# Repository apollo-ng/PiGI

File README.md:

# PiGI - A Raspberry Pi Geiger-Mueller Interface

The PiGI is built as a ready-to-go drop-in module for the Raspberry Pi to transform it
into a versatile geiger counter to measure/monitor radioactivity. It will generate the
required high voltage the counting tubes need to operate and it will safely invert the
counting impulses to a falling edge, detectable by a GPIO Pin on the PI. But it's also
designed in such a universal way in order to be  very hackable. Basically it can be
connected to any processing system that can detect falling edges like:

  * Arduino
  * ATMega
  * PIC
  * Other embedded Linux ARM/MIPS systems with GPIO Inputs (GNUBLIN, Netus G20 etc.)

## Specifications

  * 40x43mm board
  * Very low energy consumption (<2mA @ 0.09uSv/h local dose rate)
  * Cathode counting
  * Low BOM count / small footprint
  * Very cheap design: Prototype costs per board -> EUR15 / High Volume Production < 10 EUR
  * Dual stackable for low/high dosis counting with 2 tubes
  * Open-Source Hardware/Software

## Hardware

  * Schematics
  * Board designs
  * Released under CERN OHL 1.2

## Software

### Features ###

  * Live Status
  * Live (15min/60min/24h) Graphs
  * Analog gauge
  * Ion Trace Visualizer
  * History
  * Tick Simulator (For show and development)
  * Hardware RNG entropy generator
  * More to come
  * Released under GPL V3

### Screenshots ###

#### Main instrument panel

#### History instrument panel

#### Ion trace visualizer

## Website & Contact

[https://apollo.open-resource.org/lab:pigi](https://apollo.open-resource.org/lab:pigi)

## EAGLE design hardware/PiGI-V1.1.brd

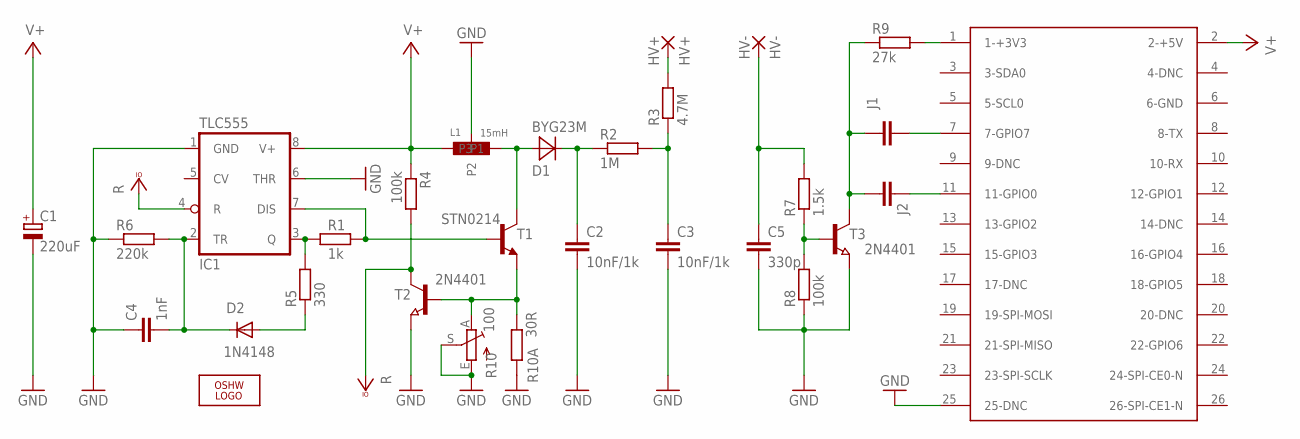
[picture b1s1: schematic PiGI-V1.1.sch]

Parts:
C1: 220uF; 153CLV-0810
C2, C3: 10nF/1k; C1206
C4: 1nF; C0805
C5: 330p; C0805
D1: BYG23M; SMA
D2: 1N4148; SOD-123_MINI-SMA
HV+: HV+; SMD2,54-5,08
HV-: HV-; SMD2,54-5,08
IC1: TLC555; SO08
J1, J2: C-EUC0805; C0805
L1: 15mH; 1200LRS
LOGO1: OSHW_LOGO_FILLX0150-NT; OSHW_FILLX150_NOTEXT
PI-GIV1.0: RASPBERRY-PI
R1: 1k; M0805
R2: 1M; R1206
R3: 4.7M; R1206
R4, R8: 100k; R0805
R5: 330; R0805
R6: 220k; R0805
R7: 1.5k; R0805
R9: 27k; R0805
R10: 100; RJ9W
R10A: 30R; M0805
T1: STN0214; SOT223
T2, T3: 2N4401; SOT23

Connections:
DIS: IC1.7 (DIS), R1.2, T1.1 (B)
GND: C1.-, C2.2, C3.2, C4.1, C5.2, IC1.1 (GND), IC1.6 (THR), L1.P4 (P2), PI-GIV1.0.25 (25-DNC), R6.1, R8.1, R10.E (A), R10.S, R10A.1, T2.2 (E), T3.2 (E)
unnamed: IC1.3 (Q), R1.1, R5.2
unnamed: D2.A, R5.1
unnamed: C2.1, D1.C, R2.1
unnamed: PI-GIV1.0.1 (1-+3V3), R9.2
unnamed: C4.2, D2.C, IC1.2 (TR), R6.2
unnamed: D1.A, L1.P3, T1.4 (C)
unnamed: R10.A (E), R10A.2, T1.3 (E), T2.1 (B)
unnamed: C3.1, R2.2, R3.1
unnamed: R7.1, R8.2, T3.1 (B)
unnamed: J1.2, J2.2, R9.1, T3.3 (C)
unnamed: C5.1, HV-.1, R7.2
unnamed: HV+.1, R3.2
unnamed: J1.1, PI-GIV1.0.7 (7-GPIO7)
unnamed: J2.1, PI-GIV1.0.11 (11-GPIO0)
V+: C1.+, IC1.8 (V+), L1.P1, PI-GIV1.0.2 (2-+5V), R4.1
VCCIO: IC1.4 (R), R4.2, T2.3 (C)

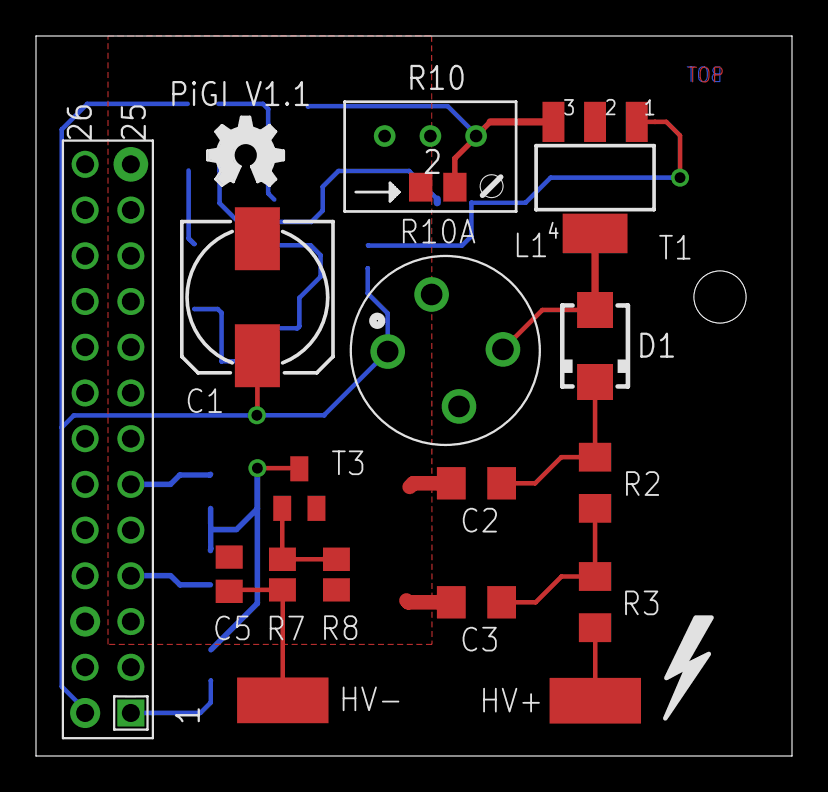
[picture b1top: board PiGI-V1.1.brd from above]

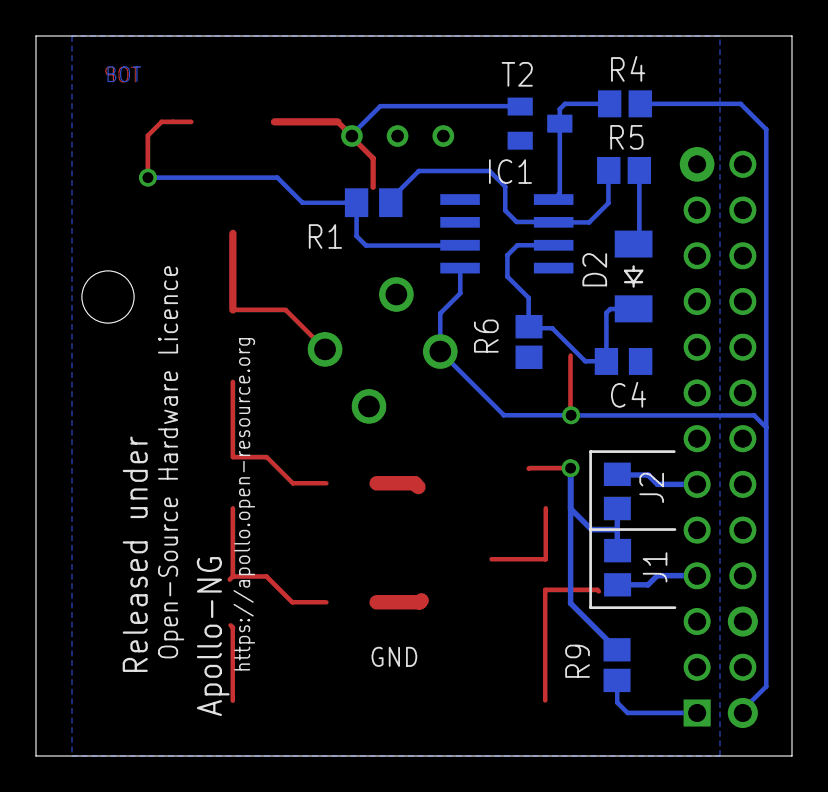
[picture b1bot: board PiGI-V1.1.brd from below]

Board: 2 copper layers, 42.0 x 40.0 mm, 29 parts (11 on the bottom side), 18 nets.

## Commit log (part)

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2013-06-08 Added V1.0 Board for the prototypes
2013-06-08 Added V1.1 (pre-production state)
2013-06-08 Added simple couter example
2013-06-08 Added some basic initial docs
2013-06-08 Updated docs
2013-06-08 More doc updates
2013-06-09 Minor position modifications of t/bnames placement on the board and clean up of schematics
2013-06-23 Added HD images of prototype board V1.0
2013-06-30 Added Image to README.md
2013-07-03 Added daemon skelleton harness (counterd4)
2013-07-03 Added software arch overview
2013-07-23 typo fixes
2014-02-09 added picoreflow stuff as boilerplate
2014-02-09 added gitignore
2014-02-09 public/index.html
2014-02-09 Fixed absoloute path asset bug
2014-02-09 Updated index.html and css for pigi basics
2014-02-09 audio example
2014-02-09 sound working, yay
2014-02-09 webserver working again on non-pi devices
2014-02-09 minimal counter simulation
2014-02-09 cpm logic
2014-02-09 included pigi gpio
2014-02-09 More pigi UI changes
2014-02-09 cpm values over websocket
2014-02-09 Added CPM update to websocket
2014-02-09 different cpm/cps calculation
2014-02-09 Testing CPS
2014-02-09 dont send only zeros for cps %)
2014-02-10 Updated README in example archive to point to pigid
2014-02-10 added counterd.py to examples
2014-02-10 adapted config to geigercounter
2014-02-10 Added Audio en/disable and counter toggling (CPM/CPS)
2014-02-10 multiclient, more values
2014-02-10 config parameter bugfix
2014-02-10 Adapted INES level indicator for quick situation determination
2014-02-10 Alternative construct for the head display (not active yet)
2014-02-10 refactoring
2014-02-10 refactoring to two sockets, audio toggle working again
2014-02-10 Added README
2014-02-10 basic logging and log delivery
2014-02-10 wrapping of loglines in history obj
2014-02-10 add timestamp to log update
2014-02-10 Added flot.time.js
2014-02-10 delay first log line after start
2014-02-10 Trying to integrate INES ruleset
2014-02-10 only send log of last 15 min
2014-02-10 only show rolling last 15 min in graph
2014-02-10 Added favicon.ico
2014-02-10 serve favicon
2014-02-11 cleanup and refeactoring
2014-02-11 init script added
2014-02-11 absolute path fixes, initscript works :)
2014-02-11 Updated README with current deps & install/usage instructions
2014-02-14 Major UI refactoring for performant mobile-first strategy
2014-02-14 Refactoring of chart and audio ticks
2014-02-14 More JQTouch updates
2014-02-14 Added missing assets and moved to column chart
2014-02-14 backlog refactoring part I
2014-02-14 backlog refactoring part II
2014-02-14 moar refactoring
2014-02-14 cleanup
2014-02-14 added nicer python examples
2014-02-14 fix in example
2014-02-14 Added analog gauge
2014-02-15 15min/60min/24h working
2014-02-15 area graph and better backlog handling
2014-02-15 log refactoring
2014-02-15 history averaging
2014-02-15 Integrated self-built jqtouch to get to latest upstream
2014-02-15 Moved MFD into toolbar
2014-02-16 better backlog 15/60min
2014-02-16 Introducing geoLocation awareness
2014-02-16 Funny effects :)
2014-02-16 Minor bugfixes
2014-02-16 backlog fix
2014-02-16 Moved chart to full viewport and integrated controls
2014-02-16 rolling avg
2014-02-16 Updated chart control and fixed gauge view
2014-02-16 nicer avg in chart
2014-02-17 js cleanup
2014-02-17 small js fixes
2014-02-17 Added visual trace canvas and js mimik
2014-02-17 Added trace to updaeLayout
2014-02-17 trace visualization
2014-02-18 Added icon-font for pigi (custom fontello.com pkg)
2014-02-18 fixed tracevisual size fnord
2014-02-18 Minor class wars
2014-02-19 Updated geoLocation indicator behaviour
2014-02-19 Minor UI upgrades
2014-02-23 Updated font icons
2014-02-24 Updated to new naming convention
2014-02-24 Added History panel
2014-02-25 Change Menus/App structure and filled history with an empty chart
2014-02-26 Some more UI refactoring
2014-02-26 bugfix attempt for status socket
2014-02-26 websocket port automagic
2014-02-26 all time history
2014-02-26 nicer format string for history
2014-02-26 Updated settings
2014-02-26 Realized md-control liquid button state
2014-02-27 more statussocket buxfix ideas
2014-02-27 trace improvements
2014-02-27 enable zoom in history
2014-02-27 all instruments resize like a charm
2014-02-27 Settings cleanup and new global event handlers
2014-02-27 Updated modal handling and back button fix for mobile
2014-02-27 Modal updates and spinner integration
2014-02-28 Modal & global event progress
2014-02-28 Updated modals and introduced dygraph charting
2014-03-01 dycharts integration for history
2014-03-01 dycharts for live log
2014-03-01 minimum for log scale
2014-03-01 fix nasty autorange bug
2014-03-01 Refactoring after dygraph integration
2014-03-01 small bugfix deadtime compensation disabled on simulation
2014-03-01 bugfix websocket error 100% cpu
2014-03-01 dysfunctional daterangepicker
2014-03-01 restored 15min avg
2014-03-01 xlabel ui fix
2014-03-01 Refactoring and pinning modals
2014-03-02 Geolocation + Modal handling refactoring progress
2014-03-02 More fixes to geo and modals
2014-03-02 There is nothing to say about that, really...
2014-03-02 Minor fixes to the last commits
2014-03-02 A little more cleanup
2014-03-02 showErrorModal manages md-show state properly now
2014-03-02 new config system
2014-03-02 Added splashscreen to give UI time to settle
2014-03-02 major org and name refactoring
2014-03-02 cleanup, fixed nasty 100% cpu bug (how did this even work before???)
2014-03-02 logging to file
2014-03-02 RADCON Table draft
2014-03-02 to much slash in init script
2014-03-02 rename pigi -> webGI in urls
2014-03-02 readded sounds %)
2014-03-02 Integrated RADCON/unit switching
2014-03-02 improved logging
2014-03-02 Fix RADCON details update bug
2014-03-02 green dot on visual trace
2014-03-02 different shade of green for trace
2014-03-02 trace looks pretty green now
2014-03-02 Integrated RADCON color scheme switching
2014-03-02 More fixes to UI reflectors
2014-03-03 fixed graph colorchange (no more manual update)
2014-03-03 Updated history instrumernt and sliding range selector
2014-03-03 fix division by zero bug
2014-03-03 zoom switching between live charts
2014-03-03 nicer hd/ld switch for live graph
2014-03-03 js completely depens on pyGI time
2014-03-03 Added tick.mp3
2014-03-03 Updated RADCON Modal
2014-03-03 Updates to RADCON
2014-03-03 Introduced basic monitoring/alerting
2014-03-03 added entropy generation
2014-03-03 Fix crude math
2014-03-04 Changed sample time of bell
2014-03-04 Added ui-bell attribution
2014-03-04 Added appropriate licenses
2014-03-04 This time for real :)
2014-03-04 Updated docs and made RADCON elements unselectable
2014-03-04 Updated README.md for new structure
2014-03-04 More README Updates
2014-03-04 Needed fix for gevent-websocket-0.9.3
2014-03-04 Typo fix
2014-03-04 Fix for the fix for gevent-websocket-0.9.3 (current pip install). It worked well in tests with 0.3.6 however :/
2014-03-04 Crude hack to get leveldb working on a fresh instance, would be better placed in the db init to check if it's a new instance I think
2014-03-04 Updated readmes
2014-03-05 Refactored get_last_totalcount for more efficiency
2014-03-05 Updated docs and added some more verbose explanations
2014-03-06 Integrated more config options to accomodate near future updates
2014-03-06 Minor cleanup
2014-03-07 Switch to geigerjson data format (Interface still broken)
2014-03-07 Interface status restored
2014-03-07 fixed last_totalcount, import WebSocketError
2014-03-07 fixed chart and logging to new geigerjson format
2014-03-07 fixed gauge and tracer to new geigerjson format
2014-03-07 bugfix chart update
2014-03-08 bugfix
2014-03-08 another bugfix
2014-03-08 some more fixes
2014-03-08 module patternf for tracer, working
2014-03-08 tracer module cleanup
2014-03-08 RADCON Fixes
2014-03-08 added js module template
2014-03-08 gauge -> module, fix for tracer module
2014-03-08 spinner -> module
2014-03-08 geo -> module
2014-03-08 ticker (audio) -> module
2014-03-08 history -> module
2014-03-08 livechart (log) -> module
2014-03-08 Some more updates & cleanup
2014-03-08 sim source
2014-03-08 RADCON Finals
2014-03-08 Add simulation data notification
2014-03-08 status -> module
2014-03-08 cleanup in webGI.js
2014-03-08 Introduced Annotations
2014-03-08 server options in webGI (sim_dose_rate for now)
2014-03-08 webGI server config persistence
2014-03-09 Integrated option slider/display for sim target settings
2014-03-09 Minor updates and initial ranger movement
2014-03-09 real dtc and no more dummy values in geigerjson
2014-03-09 annotations proof-of-concept
2014-03-09 Updated Server Options
2014-03-10 Added css only selection based suboptions
2014-03-10 Some more progress with the suboptions
2014-03-11 More serverOptionsPanel features + UI cleaning
2014-03-11 More fixes on the geo suboptions
2014-03-13 More fixes to option UI elements
2014-03-14 server options
2014-03-15 More serverOptions stuff
2014-03-15 annotations survive in 15m/60m chart
2014-03-15 added orm badge
2014-03-15 moved status websocket stuff to status module
2014-03-15 Early serverOptionsPanel draft finished
2014-03-15 Added geoSnaphot feature and annotation clickcallback (Updating existing annotations is broken)
2014-03-16 Added svg assets
2014-03-16 moved log websocket stuff to livechart module
2014-03-16 annotation bugfixes
2014-03-16 annotations in livechart mostly working
2014-03-16 show annotations in history
2014-03-16 fixed panel switching bug (livechart age)
2014-03-16 functionality for server settings in webGI
2014-03-16 Updates to badges
2014-03-16 maybe bugfix
2014-03-16 Dropped the js gauge in favor of another approach
2014-03-16 status gauge working
2014-03-16 Progress bar styling
2014-03-16 automagic uuid
2014-03-17 More about cleanups
2014-03-17 Prepared History annotation handling, showing works, saving breaks
2014-03-17 fix for annotations in history
2014-03-17 Fixed minor instrument placement/switchting issues
2014-03-17 Updated numeric input to number fields for mobile input convenience
2014-03-17 Added entropy options
2014-03-17 entropy enable/disable and pool size in webGI
2014-03-19 Updated default.cfg comments
2014-03-19 Minor redundant class sweep - unfinished, left broken serverOptions
2014-03-19 Fixed serverOptions to accept new classes
2014-03-20 Some more in depth CSS refactoring
2014-03-20 Updated webfont library
2014-03-20 Increased instrument contrast
2014-03-21 More font/glyph optimization
2014-03-21 Some late night tweakage...
2014-03-22 First media screen width tests
2014-03-22 Tick Button toggle updates icon now + some other minor things
2014-03-23 Increased multi device responsiveness of instrument-control
2014-03-23 More instrument control fixes
2014-03-24 Introduced option-checkbox classes
2014-03-25 Config options are now dynamically created by the webGI modules themselves
2014-03-25 Updated option_radio to device/browser independent/consistent styling
2014-03-25 Revalidated HTML5 and cleaned up options
2014-03-25 Updated rangeSilder and added own local grip image
2014-03-26 Corrected inline-text fontsize and line-height
2014-03-26 First work on status/gauges
2014-03-26 Setting stage for gauges/status
2014-03-26 added getter for 15min doserate avg and 24h dose
2014-03-27 Linking avg and 24h dose gauges to livechart
2014-03-27 Introduced grid for status
2014-04-01 Stripped down css, redundancy cleanup, some regres still included :)
2014-04-01 Increased display contrast for people with color perception issues
2014-05-08 Some fixes some breaks....
2014-05-08 Some fixes
2014-05-08 More cleanup
2014-05-08 Chart fixes
2014-05-09 More cleanup and bugfixes
2014-05-09 Moved alert from status into separate module and more cleanups
2014-05-10 Fixed display_num regression from last style daisycutting
2014-05-23 Changed about font size to a more readable value
2014-05-26 Added dygraph-dev-combined and some css fixes
2014-05-26 download/reset entropy (#23), reset server options (#12)
2014-06-05 More css daisycutting and a new take to fix #17
2014-06-20 new pyGI client architecture wip
2014-06-20 status websocket moved to general purpose ws
2014-06-20 ticks moved to main ws
2014-06-20 moved log websocket
2014-06-20 conf to new ws
2014-06-20 cleanup and fixmes

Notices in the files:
hardware/PiGI-V1.1.brd:
Open-Source Hardware Licence
